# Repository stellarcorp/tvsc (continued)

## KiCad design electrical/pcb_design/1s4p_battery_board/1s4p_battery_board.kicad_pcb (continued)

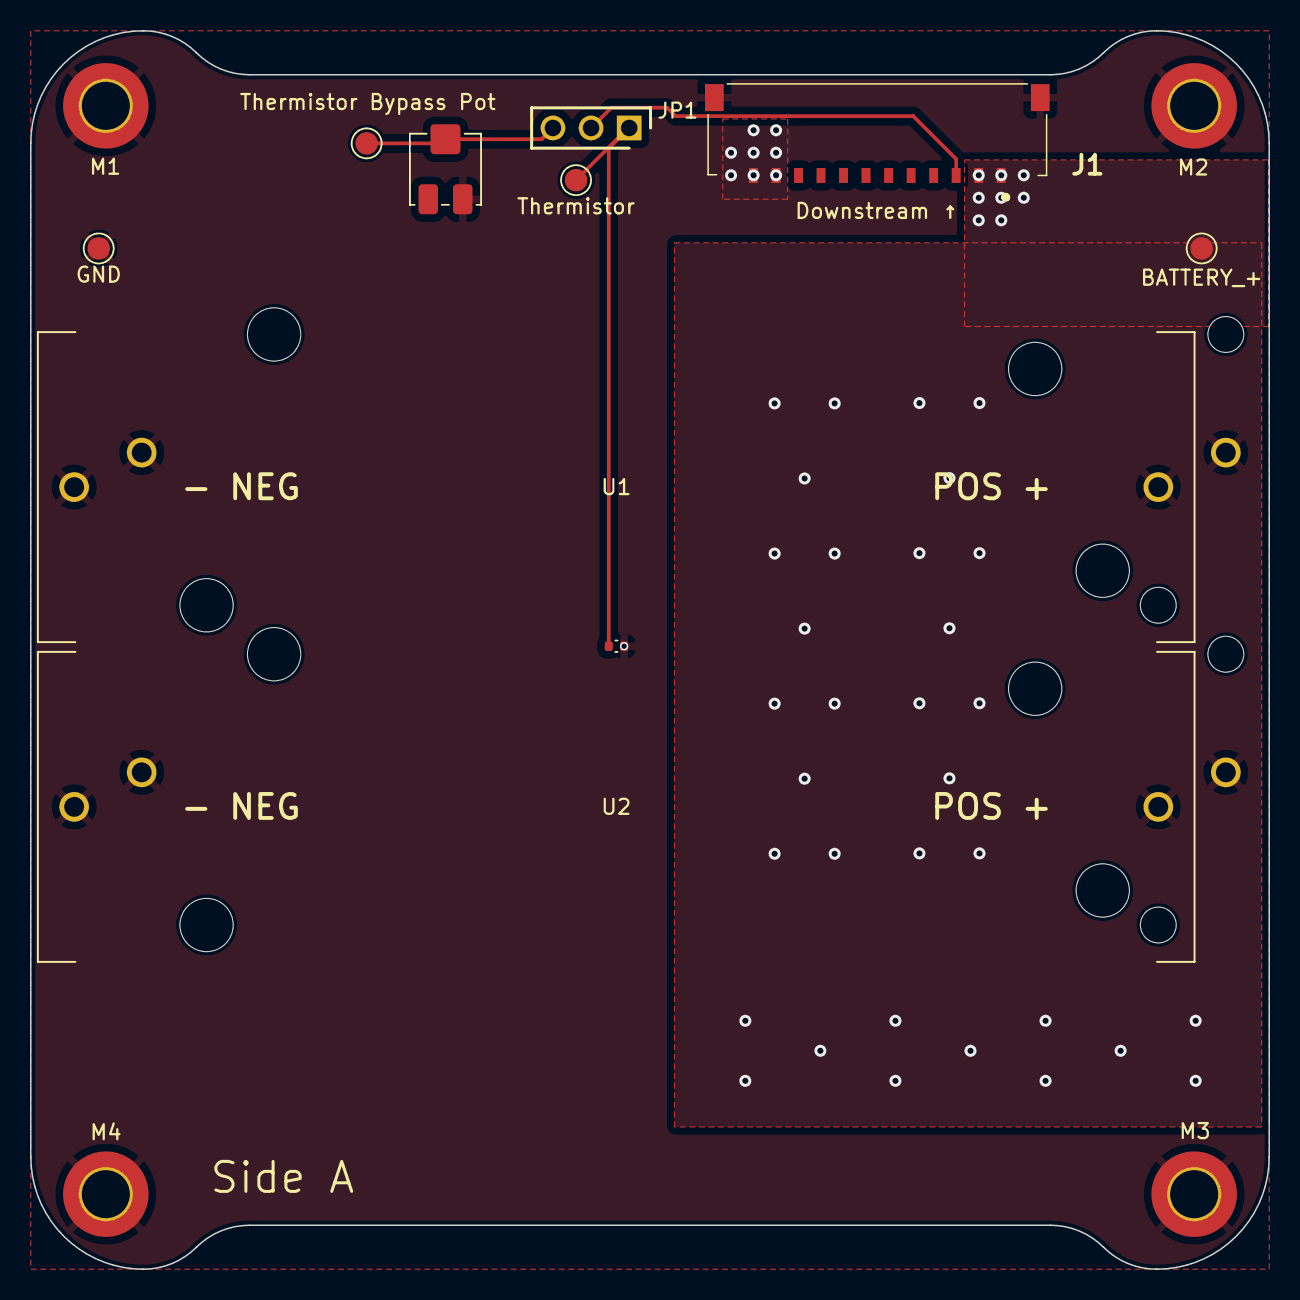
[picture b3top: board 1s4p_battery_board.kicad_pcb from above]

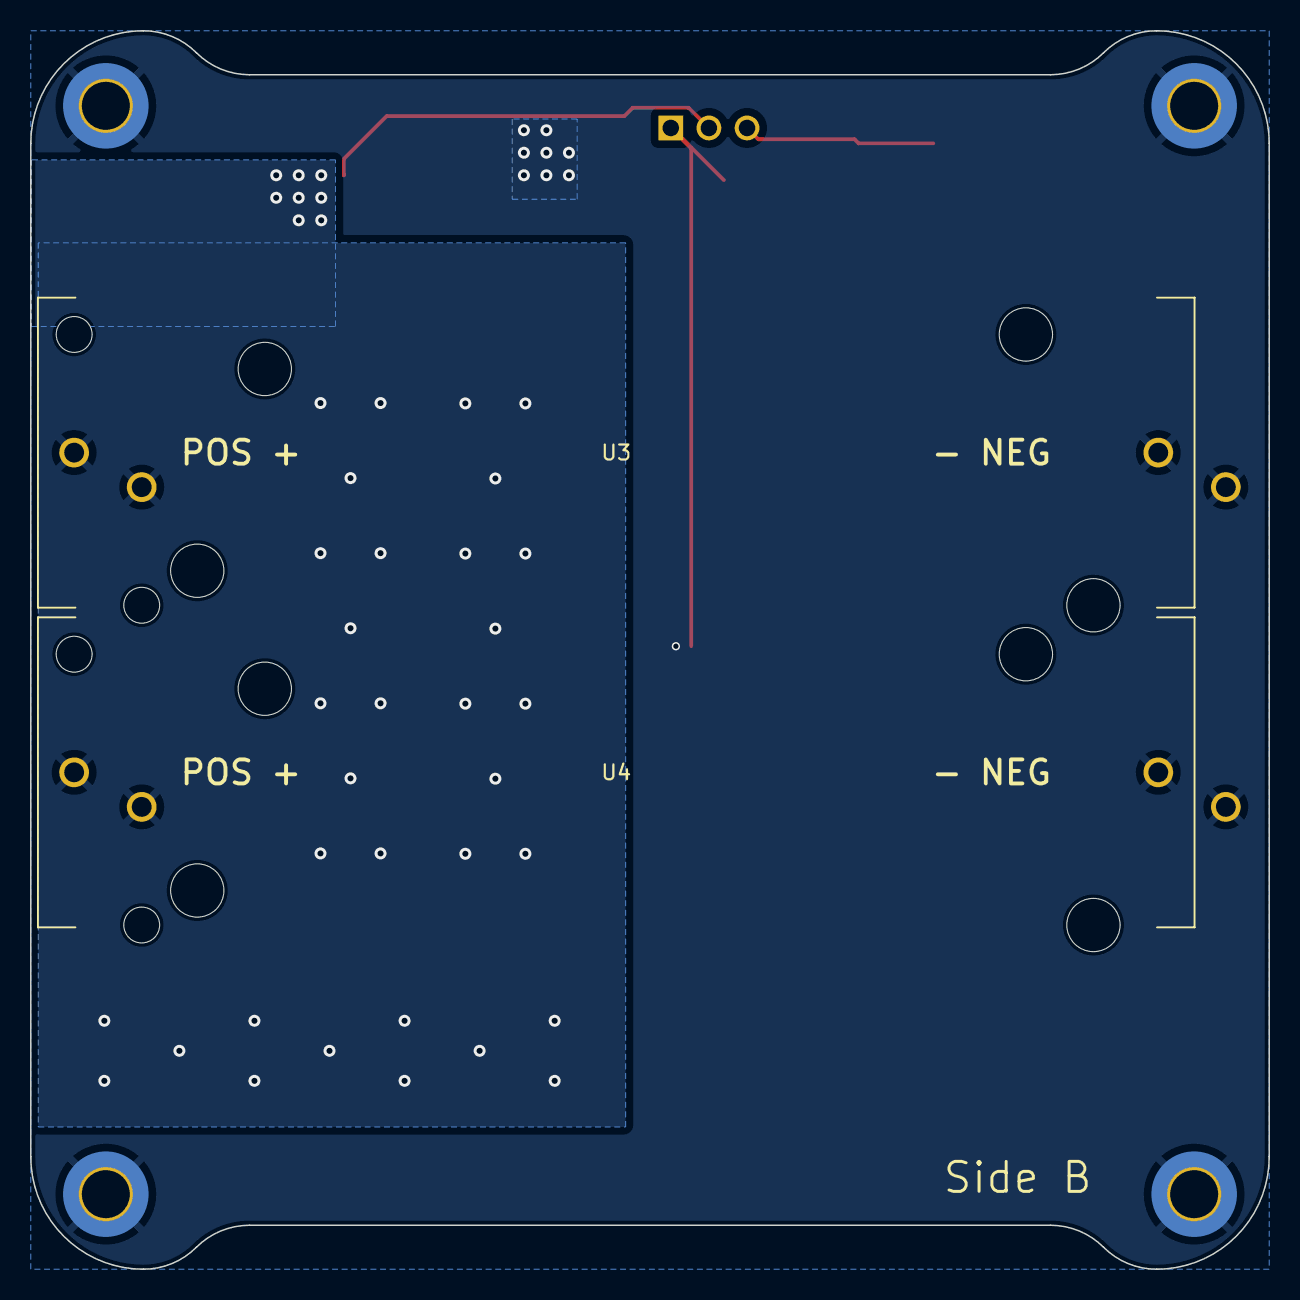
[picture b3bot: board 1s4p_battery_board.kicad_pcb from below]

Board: 2 copper layers, 82.5 x 82.5 mm, 16 parts (2 on the bottom side), 5 nets.

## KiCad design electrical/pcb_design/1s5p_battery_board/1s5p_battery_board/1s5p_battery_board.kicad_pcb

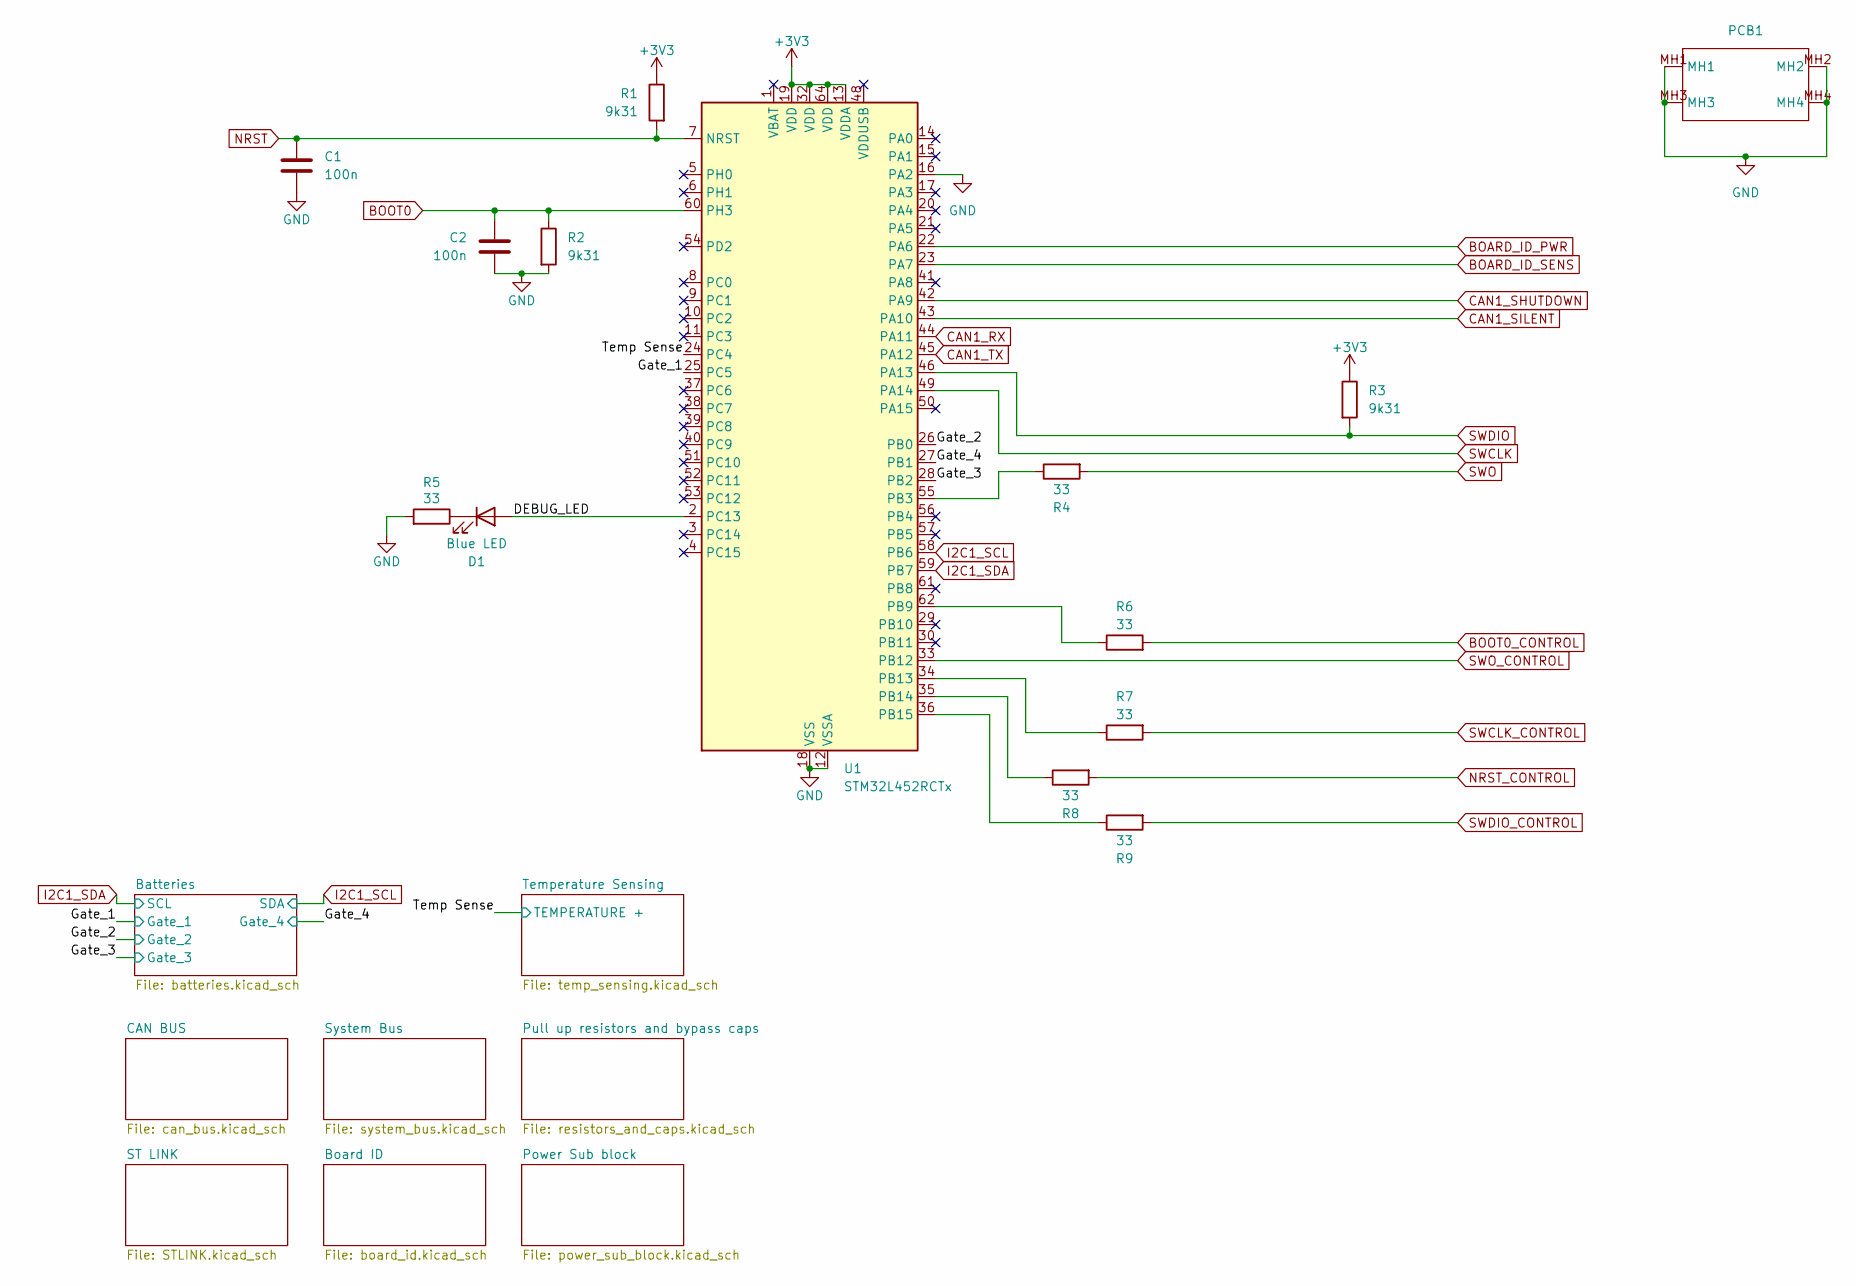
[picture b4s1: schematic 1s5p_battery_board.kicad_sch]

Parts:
C1, C2: 100n; Nondescript_C_0402_1005Metric; MPN C1525
D1: Blue LED; LED_0603_1608Metric; MPN C72041
PCB1: Core_Board_Shape_Space_Invader_2
R1, R2, R3: 9k31; Nondescript_R_0402_1005Metric; MPN C270572
R4, R5, R6, R7, R8, R9: 33; Nondescript_R_0402_1005Metric; MPN C25105
U1: STM32L452RCTx; LQFP-64_10x10mm_P0.5mm

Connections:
+3V3: R1.1, R3.1, U1.13 (VDDA), U1.19 (VDD), U1.32 (VDD), U1.64 (VDD); also elsewhere on the board
/DEBUG_LED: D1.2 (A), U1.2 (PC13)
/Gate_1: U1.25 (PC5); also elsewhere on the board
/Gate_2: U1.26 (PB0); also elsewhere on the board
/Gate_3: U1.28 (PB2); also elsewhere on the board
/Gate_4: U1.27 (PB1); also elsewhere on the board
/Temp Sense: U1.24 (PC4); also elsewhere on the board
BOARD_ID_PWR: U1.22 (PA6); also elsewhere on the board
BOARD_ID_SENS: U1.23 (PA7); also elsewhere on the board
BOOT0: C2.1, R2.1, U1.60 (PH3); also elsewhere on the board
BOOT0_CONTROL: R6.2; also elsewhere on the board
CAN1_RX: U1.44 (PA11); also elsewhere on the board
CAN1_SHUTDOWN: U1.42 (PA9); also elsewhere on the board
CAN1_SILENT: U1.43 (PA10); also elsewhere on the board
CAN1_TX: U1.45 (PA12); also elsewhere on the board
GND: C1.2, C2.2, PCB1.MH1, PCB1.MH2, PCB1.MH3, PCB1.MH4, R2.2, R5.2, U1.12 (VSSA), U1.16 (PA2), U1.18 (VSS), U1.31 (VSS), U1.47 (VSS), U1.63 (VSS); also elsewhere on the board
I2C1_SCL: U1.58 (PB6); also elsewhere on the board
I2C1_SDA: U1.59 (PB7); also elsewhere on the board
NRST: C1.1, R1.2, U1.7 (NRST); also elsewhere on the board
NRST_CONTROL: R8.2; also elsewhere on the board
unnamed: D1.1 (K), R5.1
unnamed: R4.1, U1.55 (PB3)
unnamed: R6.1, U1.62 (PB9)
unnamed: R7.1, U1.34 (PB13)
unnamed: R8.1, U1.35 (PB14)
unnamed: R9.1, U1.36 (PB15)
SWCLK: U1.49 (PA14); also elsewhere on the board
SWCLK_CONTROL: R7.2; also elsewhere on the board
SWDIO: R3.2, U1.46 (PA13); also elsewhere on the board
SWDIO_CONTROL: R9.2; also elsewhere on the board
SWO: R4.2; also elsewhere on the board
SWO_CONTROL: U1.33 (PB12); also elsewhere on the board

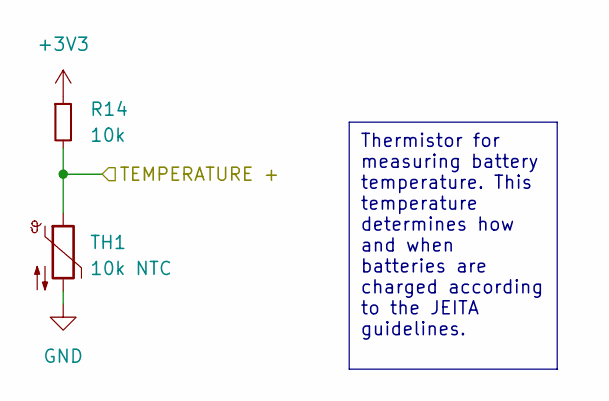
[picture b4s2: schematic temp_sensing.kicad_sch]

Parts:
R14: 10k; Nondescript_R_0402_1005Metric
TH1: 10k NTC; Nondescript_R_0402_1005Metric; MPN C336815

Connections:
+3V3: R14.1; also elsewhere on the board
/Temp Sense: R14.2, TH1.1; also elsewhere on the board
GND: TH1.2; also elsewhere on the board

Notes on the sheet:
Thermistor for measuring battery temperature. This temperature determines how and when batteries are charged according to the JEITA guidelines.

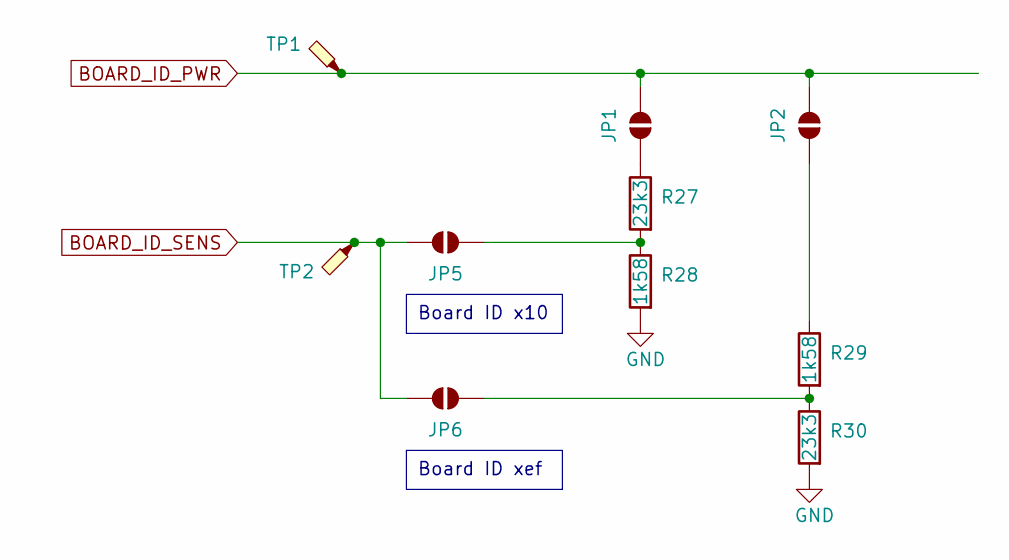
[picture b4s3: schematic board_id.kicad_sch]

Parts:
JP1, JP2, JP5, JP6: SolderJumper_2_Open; SolderJumper-2_P1.3mm_Open_RoundedPad1.0x1.5mm; MPN NA
R27, R30: 23k3; Nondescript_R_0402_1005Metric; MPN C11476
R28, R29: 1k58; Nondescript_R_0402_1005Metric; MPN C25914
TP1, TP2: TestPoint_Probe; TestPoint_Pad_D2.5mm; MPN NA

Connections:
BOARD_ID_PWR: JP1.1 (A), JP2.1 (A), TP1.1; also elsewhere on the board
BOARD_ID_SENS: JP5.1 (A), JP6.1 (A), TP2.1; also elsewhere on the board
GND: R28.2, R30.2; also elsewhere on the board
unnamed: JP1.2 (B), R27.1
unnamed: JP2.2 (B), R29.1
unnamed: JP5.2 (B), R27.2, R28.1
unnamed: JP6.2 (B), R29.2, R30.1

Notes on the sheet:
Board ID xef
Board ID x10

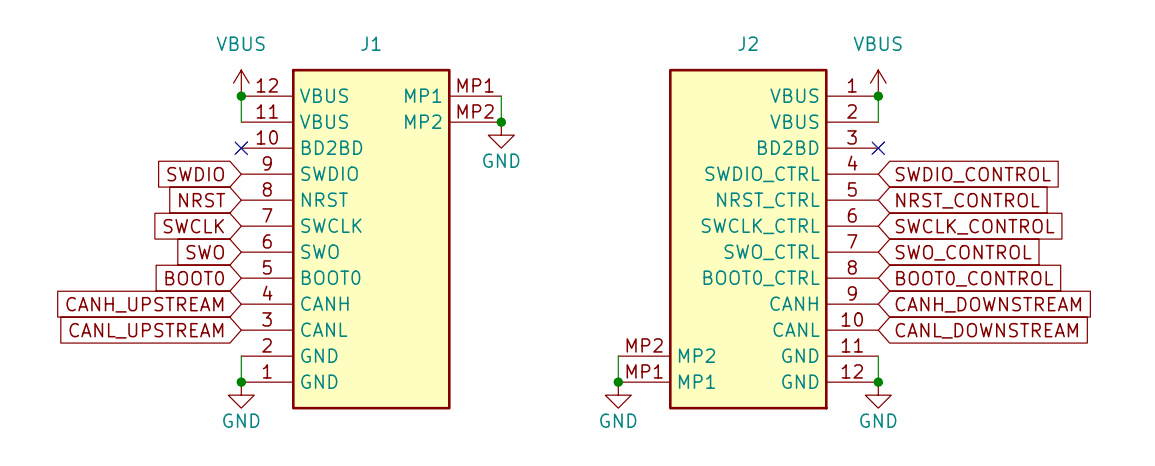
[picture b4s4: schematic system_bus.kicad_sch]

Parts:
J1: Molex_504050-1291; Bus Connector (Target); Manufacturer Part Number 504050-1291
J2: Molex_504050-1291; Bus Connector (Control); Manufacturer Part Number 504050-1291

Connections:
BOOT0: J1.5 (BOOT0); also elsewhere on the board
BOOT0_CONTROL: J2.8 (BOOT0_CTRL); also elsewhere on the board
CANH_DOWNSTREAM: J2.9 (CANH); also elsewhere on the board
CANH_UPSTREAM: J1.4 (CANH); also elsewhere on the board
CANL_DOWNSTREAM: J2.10 (CANL); also elsewhere on the board
CANL_UPSTREAM: J1.3 (CANL); also elsewhere on the board
GND: J1.1 (GND), J1.2 (GND), J1.MP1, J1.MP2, J2.11 (GND), J2.12 (GND), J2.MP1, J2.MP2; also elsewhere on the board
NRST: J1.8 (NRST); also elsewhere on the board
NRST_CONTROL: J2.5 (NRST_CTRL); also elsewhere on the board
SWCLK: J1.7 (SWCLK); also elsewhere on the board
SWCLK_CONTROL: J2.6 (SWCLK_CTRL); also elsewhere on the board
SWDIO: J1.9 (SWDIO); also elsewhere on the board
SWDIO_CONTROL: J2.4 (SWDIO_CTRL); also elsewhere on the board
SWO: J1.6 (SWO); also elsewhere on the board
SWO_CONTROL: J2.7 (SWO_CTRL); also elsewhere on the board
VBUS: J1.11 (VBUS), J1.12 (VBUS), J2.1 (VBUS), J2.2 (VBUS); also elsewhere on the board

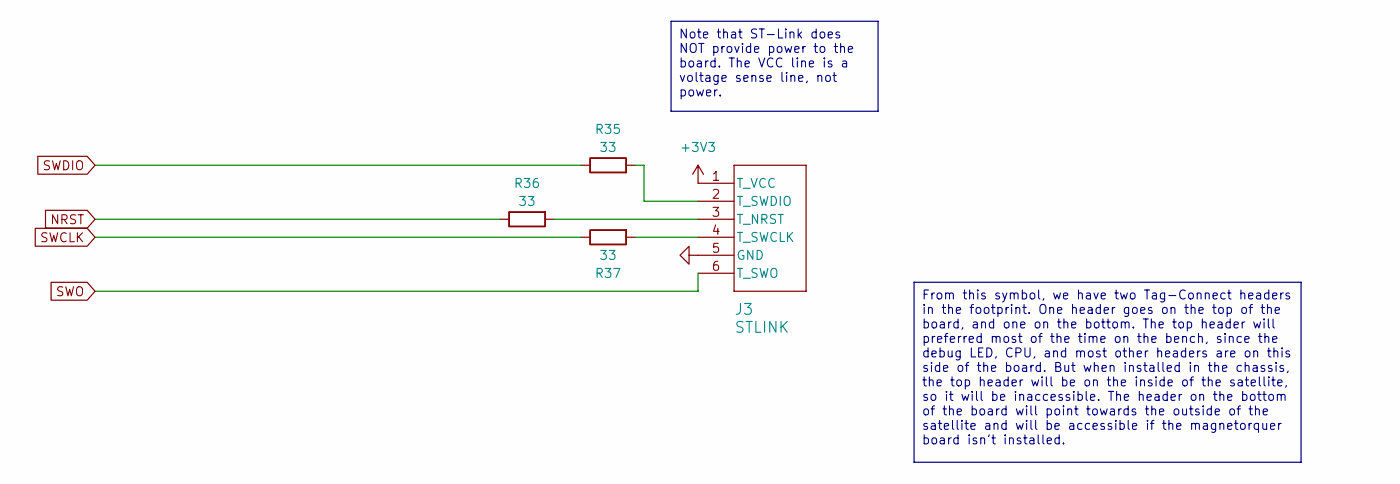
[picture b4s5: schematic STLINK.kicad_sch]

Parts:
J3: STLINK; Double-Sided_Tag-Connect_TC2030-IDC-NL_2x03_P1.27mm_Vertical; MPN NA
R35, R36, R37: 33; Nondescript_R_0402_1005Metric; MPN C25105

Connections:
+3V3: J3.1 (T_VCC); also elsewhere on the board
GND: J3.5 (GND); also elsewhere on the board
NRST: R36.1; also elsewhere on the board
unnamed: J3.3 (T_NRST), R36.2
unnamed: J3.4 (T_SWCLK), R37.2
unnamed: J3.2 (T_SWDIO), R35.2
SWCLK: R37.1; also elsewhere on the board
SWDIO: R35.1; also elsewhere on the board
SWO: J3.6 (T_SWO); also elsewhere on the board

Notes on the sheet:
Note that ST-Link does NOT provide power to the board. The VCC line is a voltage sense line, not power.
From this symbol, we have two Tag-Connect headers in the footprint. One header goes on the top of the board, and one on the bottom. The top header will preferred most of the time on the bench, since the debug LED, CPU, and most other headers are on this side of the board. But when installed in the 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

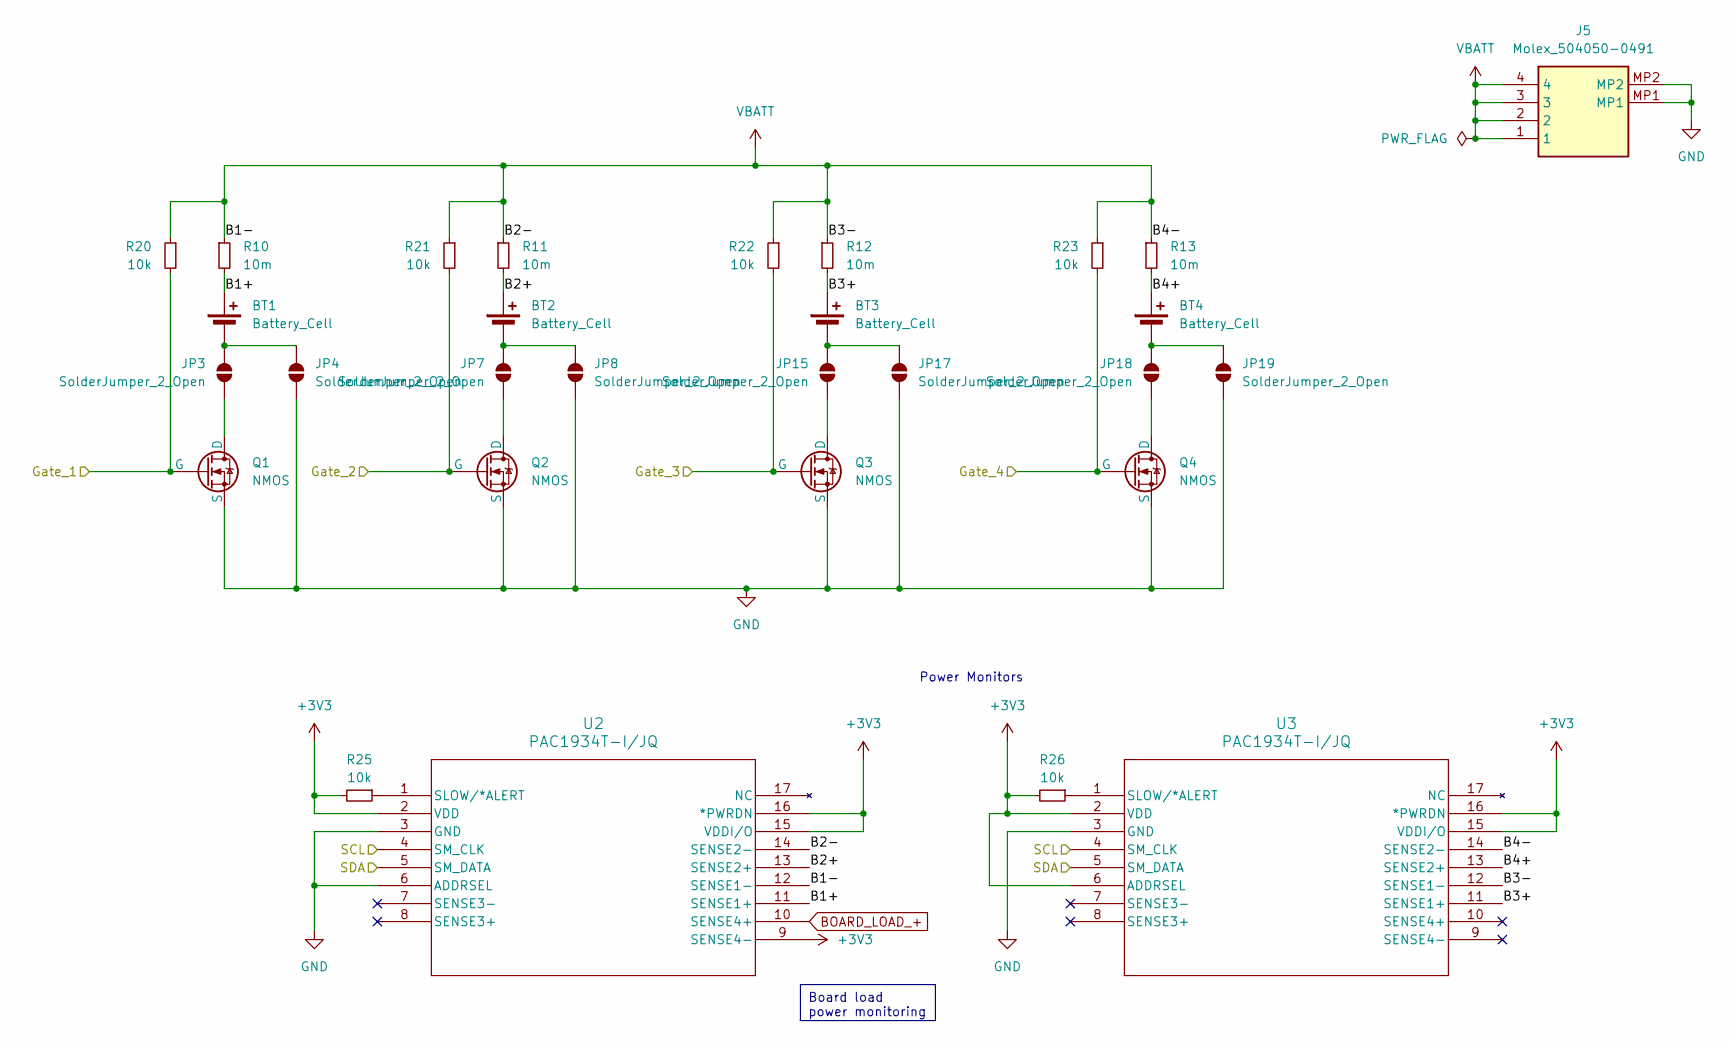
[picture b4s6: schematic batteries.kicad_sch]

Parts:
BT1, BT2, BT3, BT4: Battery_Cell; BAT_1043
J5: Molex_504050-0491; Manufacturer Part Number 504050-0491
JP3, JP4, JP7, JP8, JP15, JP17, JP18, JP19: SolderJumper_2_Open; SolderJumper-2_P1.3mm_Open_RoundedPad1.0x1.5mm
Q1, Q2, Q3, Q4: NMOS; SOT-23
R10, R11, R12, R13: 10m; R_1206_3216Metric
R20, R21, R22, R23, R25, R26: 10k; Nondescript_R_0402_1005Metric
U2, U3: PAC1934T-I/JQ; QFN16

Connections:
+3V3: R25.2, R26.2, U2.2 (VDD), U2.9 (SENSE4-), U2.15 (VDDI/O), U2.16 (*PWRDN), U3.2 (VDD), U3.6 (ADDRSEL), U3.15 (VDDI/O), U3.16 (*PWRDN); also elsewhere on the board
/Batteries/B1+: BT1.P (+), R10.2, U2.11 (SENSE1+)
/Batteries/B2+: BT2.P (+), R11.2, U2.13 (SENSE2+)
/Batteries/B3+: BT3.P (+), R12.2, U3.11 (SENSE1+)
/Batteries/B4+: BT4.P (+), R13.2, U3.13 (SENSE2+)
/Gate_1: Q1.2 (G), R20.2; also elsewhere on the board
/Gate_2: Q2.2 (G), R21.2; also elsewhere on the board
/Gate_3: Q3.2 (G), R22.2; also elsewhere on the board
/Gate_4: Q4.2 (G), R23.2; also elsewhere on the board
BOARD_LOAD_+: U2.10 (SENSE4+); also elsewhere on the board
GND: J5.MP1, J5.MP2, JP4.1 (A), JP8.1 (A), JP17.1 (A), JP19.1 (A), Q1.3 (S), Q2.3 (S), Q3.3 (S), Q4.3 (S), U2.3 (GND), U2.6 (ADDRSEL), U3.3 (GND); also elsewhere on the board
I2C1_SCL: U2.5 (SM_DATA), U3.5 (SM_DATA); also elsewhere on the board
I2C1_SDA: U2.4 (SM_CLK), U3.4 (SM_CLK); also elsewhere on the board
unnamed: BT1.N (-), JP3.2 (B), JP4.2 (B)
unnamed: BT2.N (-), JP7.2 (B), JP8.2 (B)
unnamed: BT3.N (-), JP15.2 (B), JP17.2 (B)
unnamed: BT4.N (-), JP18.2 (B), JP19.2 (B)
unnamed: JP3.1 (A), Q1.1 (D)
unnamed: JP7.1 (A), Q2.1 (D)
unnamed: JP15.1 (A), Q3.1 (D)
unnamed: JP18.1 (A), Q4.1 (D)
unnamed: R25.1, U2.1 (SLOW/*ALERT)
unnamed: R26.1, U3.1 (SLOW/*ALERT)
VBATT: J5.1, J5.2, J5.3, J5.4, R10.1, R11.1, R12.1, R13.1, R20.1, R21.1, R22.1, R23.1, U2.12 (SENSE1-), U2.14 (SENSE2-), U3.12 (SENSE1-), U3.14 (SENSE2-); also elsewhere on the board

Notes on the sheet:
Board load power monitoring
Power Monitors

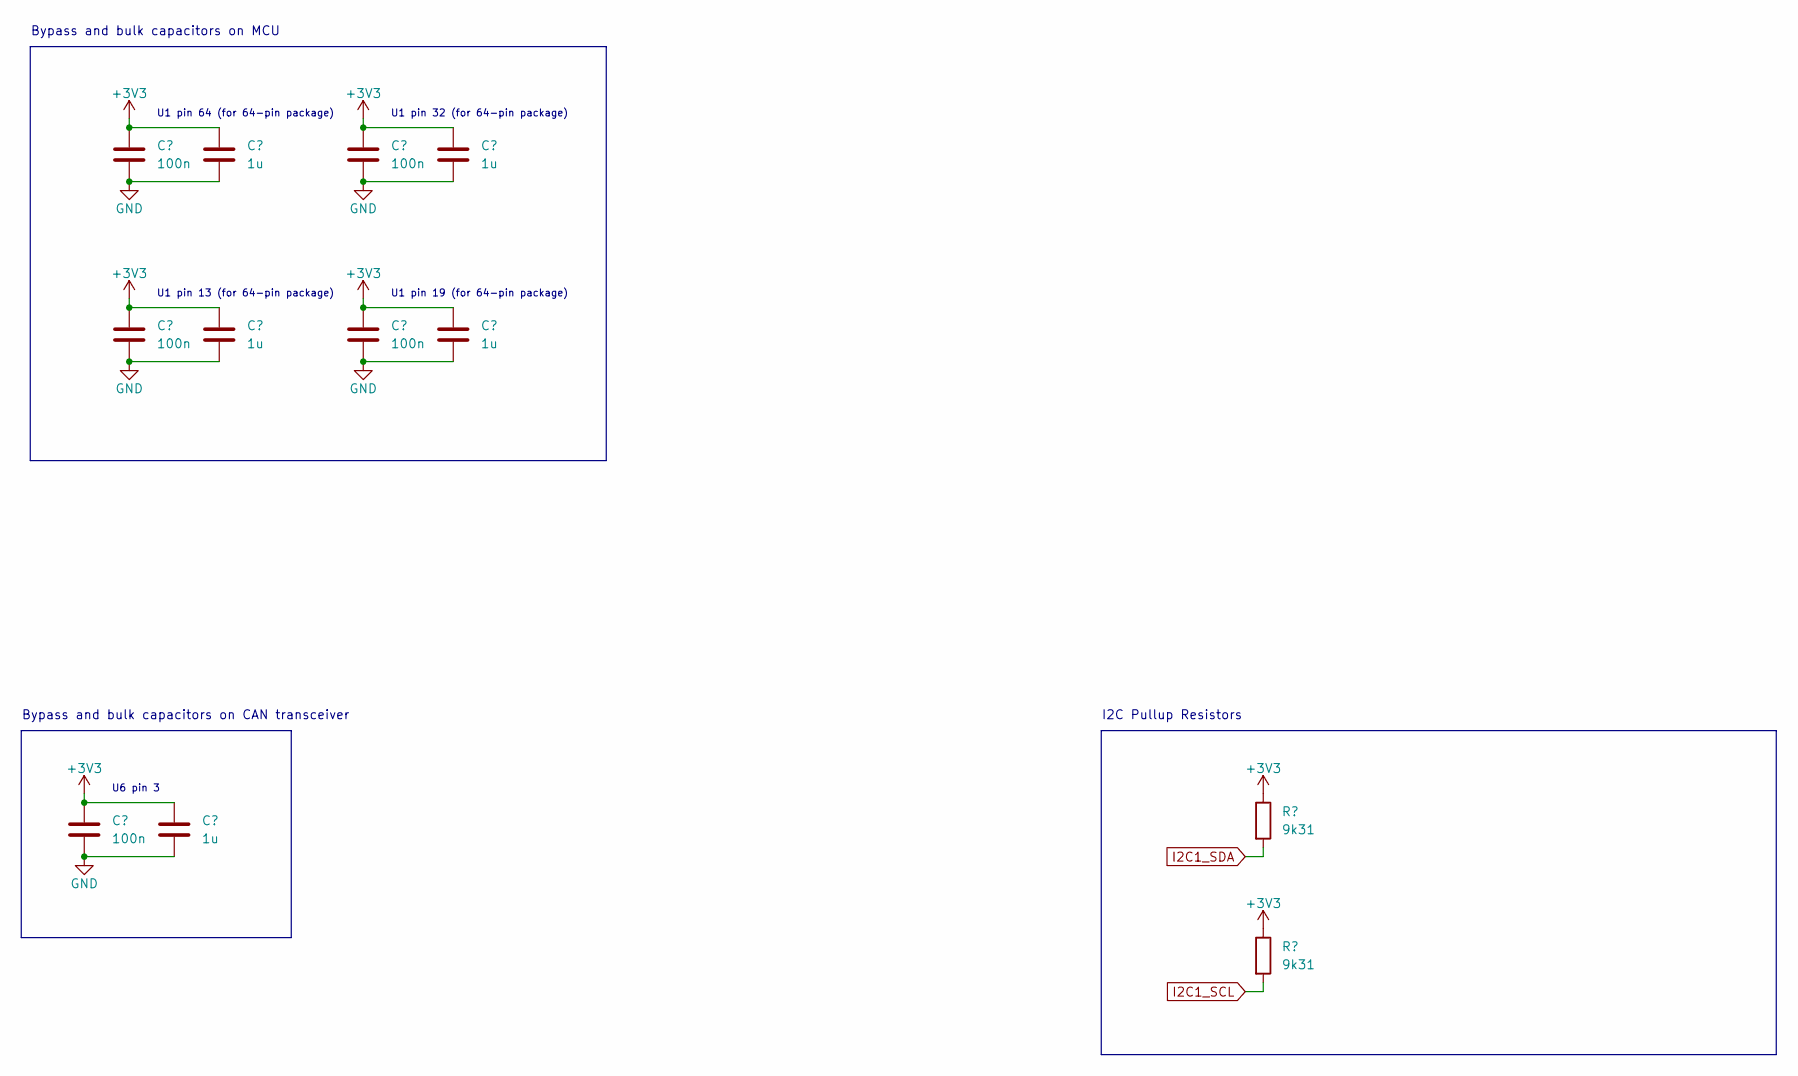
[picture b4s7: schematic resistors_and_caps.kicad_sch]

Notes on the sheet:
U6 pin 3
U1 pin 64 (for 64-pin package)
I2C Pullup Resistors
U1 pin 32 (for 64-pin package)
U1 pin 19 (for 64-pin package)
U1 pin 13 (for 64-pin package)
Bypass and bulk capacitors on CAN transceiver
Bypass and bulk capacitors on MCU

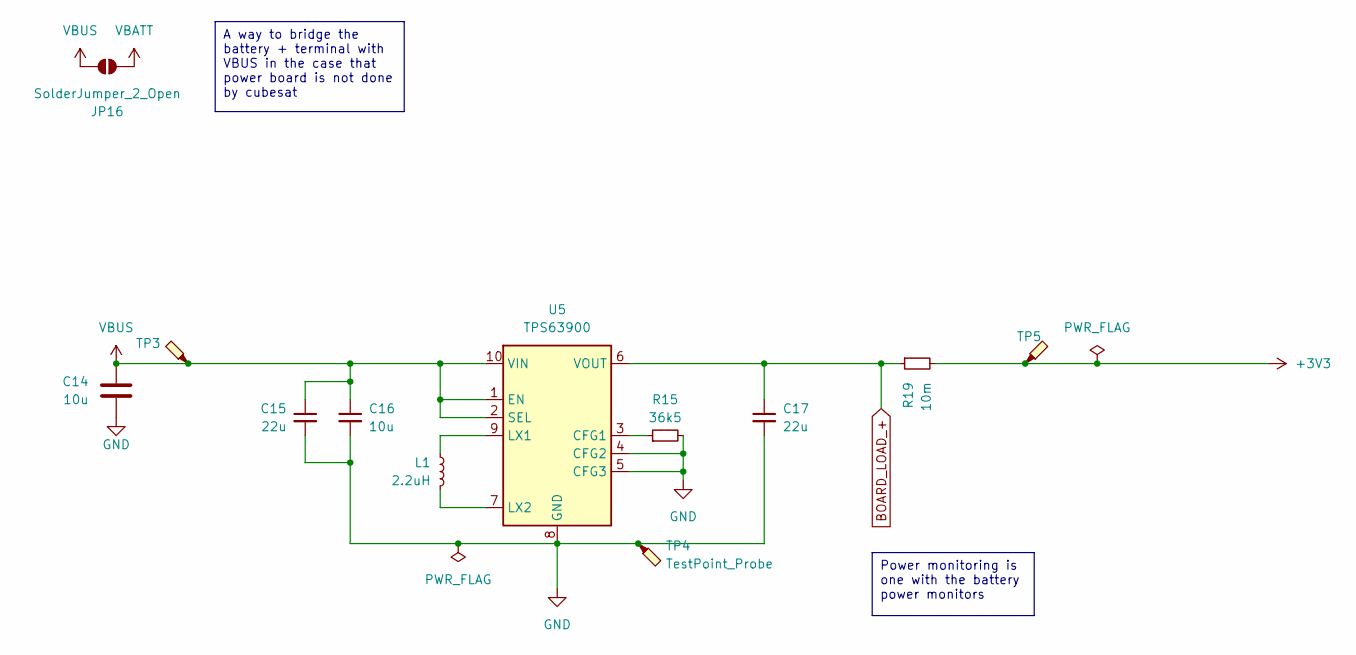
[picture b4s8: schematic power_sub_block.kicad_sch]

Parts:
C14: 10u; Nondescript_C_0402_1005Metric; MPN C15525
C15, C17: 22u; Nondescript_C_0603_1608Metric
C16: 10u; Nondescript_C_0603_1608Metric
JP16: SolderJumper_2_Open; SolderJumper-2_P1.3mm_Open_RoundedPad1.0x1.5mm
L1: 2.2uH; L_1008_2520Metric
R15: 36k5; Nondescript_R_0603_1608Metric
R19: 10m; Nondescript_R_0402_1005Metric
TP3, TP5: TestPoint_Probe; TestPoint_Pad_D2.5mm; MPN NA
TP4: TestPoint_Probe; TestPoint_Pad_D2.5mm
U5: TPS63900; WSON-10-1EP_2.5x2.5mm_P0.5mm_EP1.2x2mm

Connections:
+3V3: R19.2, TP5.1; also elsewhere on the board
BOARD_LOAD_+: C17.1, R19.1, U5.6 (VOUT); also elsewhere on the board
GND: C14.2, C15.2, C16.2, C17.2, R15.2, TP4.1, U5.4 (CFG2), U5.5 (CFG3), U5.8 (GND), U5.11 (GND); also elsewhere on the board
unnamed: R15.1, U5.3 (CFG1)
unnamed: L1.2, U5.9 (LX1)
unnamed: L1.1, U5.7 (LX2)
VBATT: JP16.1 (A); also elsewhere on the board
VBUS: C14.1, C15.1, C16.1, JP16.2 (B), TP3.1, U5.1 (EN), U5.2 (SEL), U5.10 (VIN); also elsewhere on the board

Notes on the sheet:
Power monitoring is one with the battery power monitors
A way to bridge the battery + terminal with VBUS in the case that power board is not done by cubesat

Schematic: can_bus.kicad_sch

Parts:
C3: 100n; Nondescript_C_0402_1005Metric; MPN C1525
JP9, JP10, JP11, JP12, JP13, JP14: SolderJumper_2_Open; SolderJumper-2_P1.3mm_Open_RoundedPad1.0x1.5mm; MPN NA
RV1, RV2: 60; Nondescript_R_0402_1005Metric; MPN C60310
U4: TCAN330DR; SOIC127P600X175-8N; Manufacturer Part Number TCAN330DR

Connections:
+3V3: U4.3 (VCC); also elsewhere on the board
CAN1_RX: U4.4 (RXD); also elsewhere on the board
CAN1_SHUTDOWN: U4.5 (SHDN); also elsewhere on the board
CAN1_SILENT: U4.8 (S); also elsewhere on the board
CAN1_TX: U4.1 (TXD); also elsewhere on the board
CANH_DOWNSTREAM: JP11.2 (B); also elsewhere on the board
CANH_UPSTREAM: JP10.1 (A); also elsewhere on the board
CANL_DOWNSTREAM: JP13.2 (B); also elsewhere on the board
CANL_UPSTREAM: JP12.1 (A); also elsewhere on the board
GND: C3.1, U4.2 (GND); also elsewhere on the board
unnamed: C3.2, RV1.2, RV2.1
unnamed: JP9.2 (B), RV1.1
unnamed: JP9.1 (A), JP10.2 (B), JP11.1 (A), U4.7 (CANH)
unnamed: JP12.2 (B), JP13.1 (A), JP14.2 (B), U4.6 (CANL)
unnamed: JP14.1 (A), RV2.2

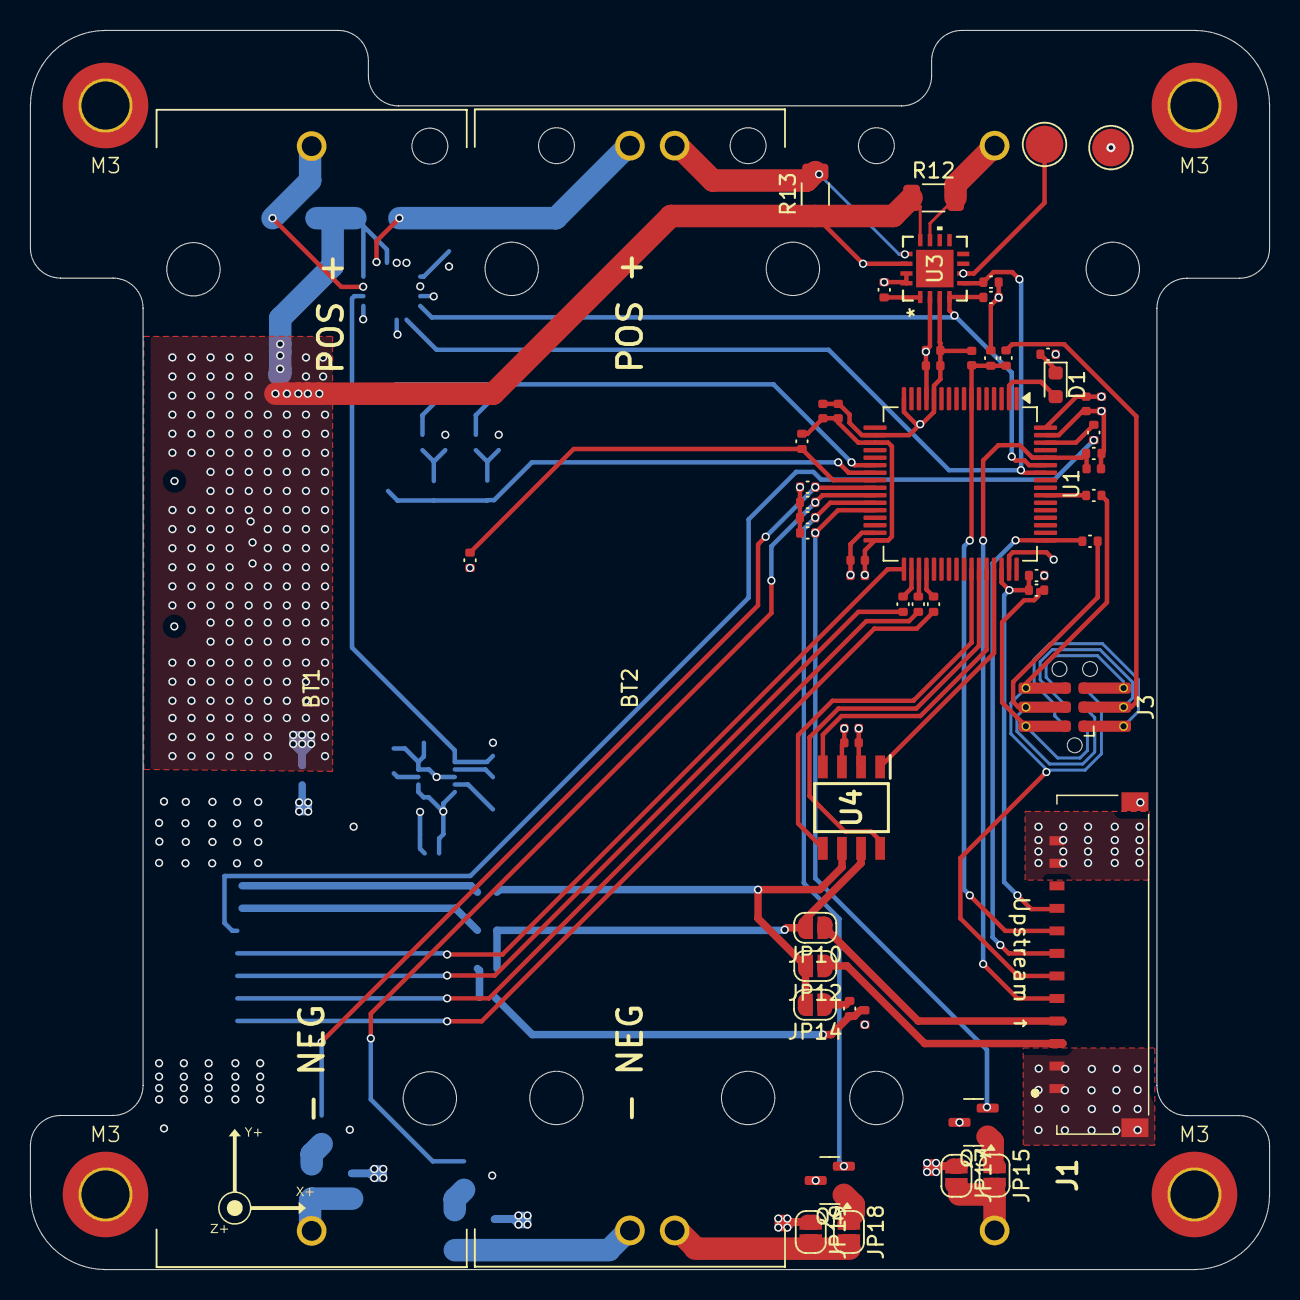
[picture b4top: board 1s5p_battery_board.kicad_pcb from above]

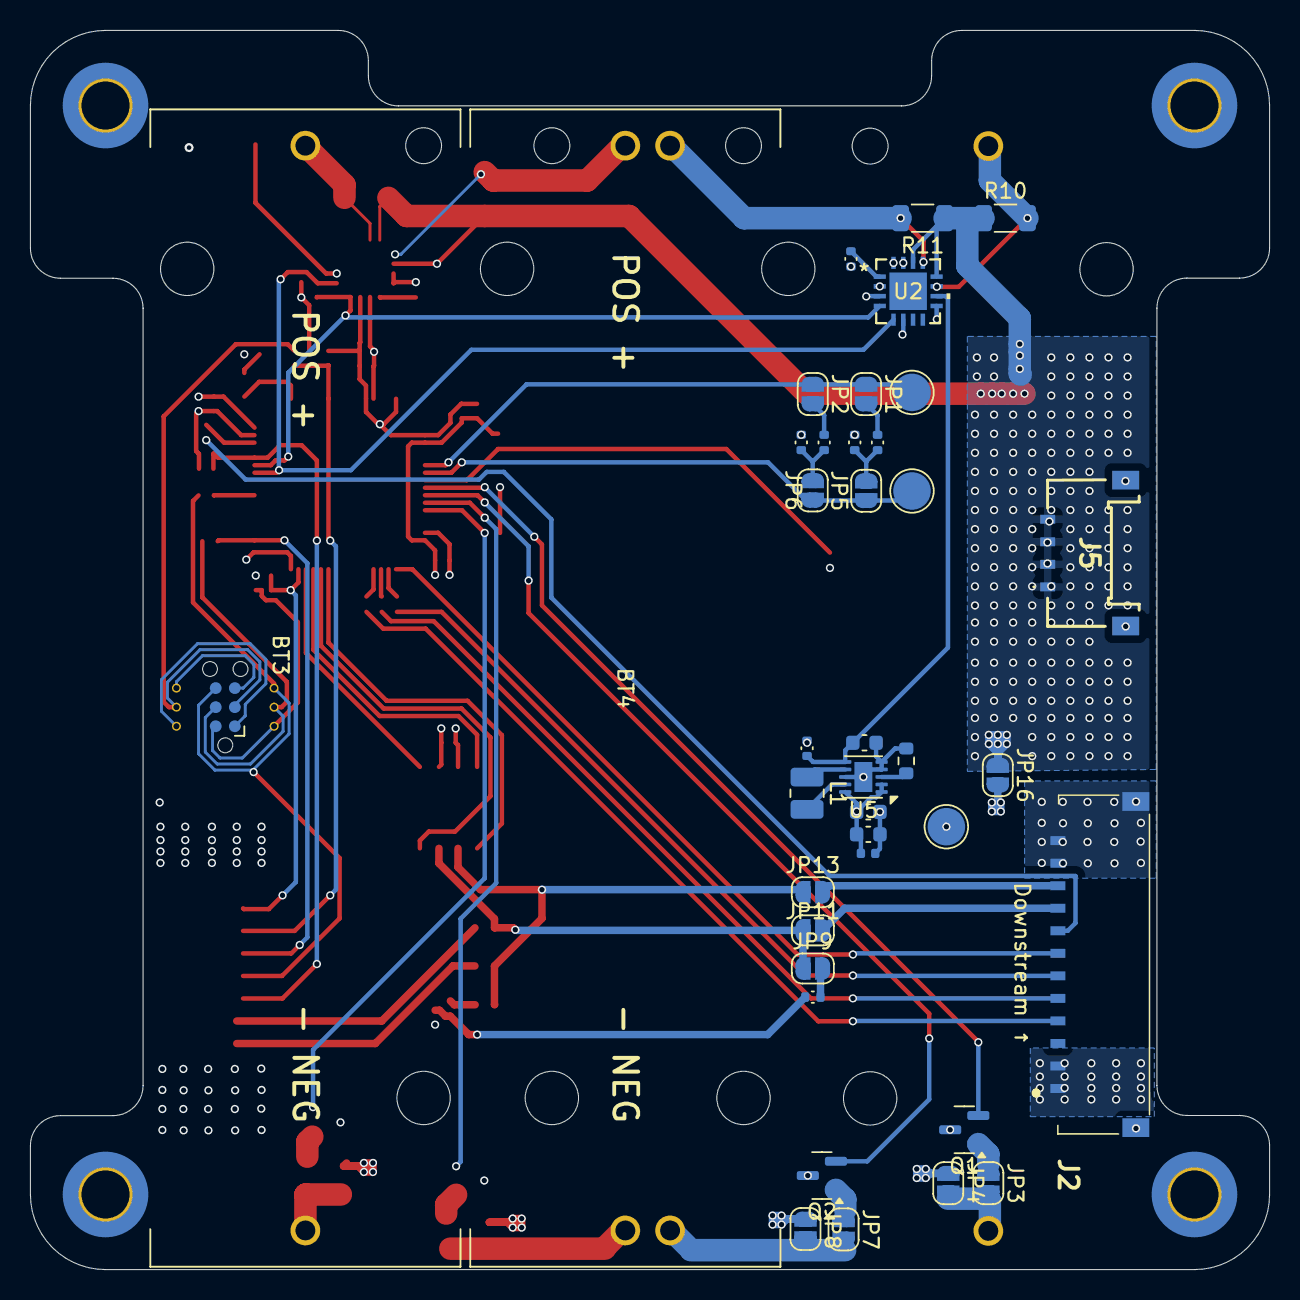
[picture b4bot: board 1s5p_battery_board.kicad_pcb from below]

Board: 4 copper layers, 82.5 x 82.5 mm, 95 parts (38 on the bottom side), 68 nets.

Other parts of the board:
C4, C6, C8, C10, C12: 100n; Nondescript_C_0402_1005Metric
C5, C7, C9, C11, C13: 1u; Nondescript_C_0402_1005Metric
R38, R39: 9k31; Nondescript_R_0402_1005Metric

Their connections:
+3V3: C4.1, C5.1, C6.1, C7.1, C8.1, C9.1, C10.1, C11.1, C12.1, C13.1, R38.1, R39.1; also elsewhere on the board
GND: C4.2, C5.2, C6.2, C7.2, C8.2, C9.2, C10.2, C11.2, C12.2, C13.2; also elsewhere on the board
I2C1_SCL: R39.2; also elsewhere on the board
I2C1_SDA: R38.2; also elsewhere on the board
